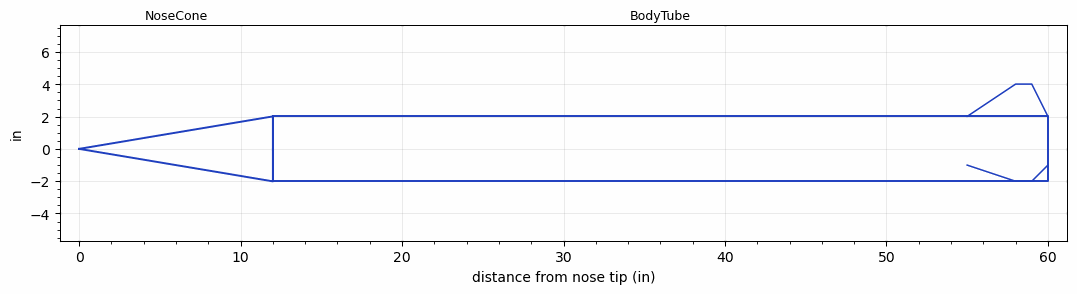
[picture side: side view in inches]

<RASAeroDocument>
 <FileVersion>2</FileVersion>
 <RocketDesign>
  <NoseCone>
   <Length>12</Length>
   <Diameter>4.024</Diameter>
   <Shape>Conical</Shape>
   <Location>0</Location>
  </NoseCone>
  <BodyTube>
   <Length>48</Length>
   <Diameter>4.024</Diameter>
   <LaunchLugDiameter>0.5</LaunchLugDiameter>
   <LaunchLugLength>0.5</LaunchLugLength>
   <Location>12</Location>
   <Fin>
    <Count>3</Count>
    <Chord>5</Chord>
    <Span>2</Span>
    <SweepDistance>3</SweepDistance>
    <TipChord>1</TipChord>
    <Thickness>0.125</Thickness>
    <LERadius>0.125</LERadius>
    <Location>5</Location>
    <AirfoilSection>Hexagonal</AirfoilSection>
    <FX1>0.125</FX1>
    <FX3>0.125</FX3>
   </Fin>
  </BodyTube>
  <Surface>Smooth (Zero Roughness)</Surface>
  <ModifiedBarrowman>False</ModifiedBarrowman>
  <Turbulence>False</Turbulence>
  <UseBooster1>False</UseBooster1>
  <UseBooster2>False</UseBooster2>
 </RocketDesign>
 <LaunchSite>
  <Altitude>3000</Altitude>
  <Pressure>30.3</Pressure>
  <RodAngle>1</RodAngle>
  <RodLength>25</RodLength>
  <Temperature>90</Temperature>
  <WindSpeed>12</WindSpeed>
 </LaunchSite>
 <Recovery>
  <Altitude1>1000</Altitude1>
  <Altitude2>1000</Altitude2>
  <DeviceType1>None</DeviceType1>
  <DeviceType2>None</DeviceType2>
  <Event1>False</Event1>
  <Event2>False</Event2>
  <Size1>1</Size1>
  <Size2>1</Size2>
  <EventType1>None</EventType1>
  <EventType2>None</EventType2>
  <CD1>1.33</CD1>
  <CD2>1.33</CD2>
 </Recovery>
 <SimulationList>
  <Simulation>
   <SustainerEngine>L1050-BS-P  (CTI)</SustainerEngine>
   <SustainerLaunchWt>40</SustainerLaunchWt>
   <SustainerNozzleDiameter>3.5</SustainerNozzleDiameter>
   <SustainerCG>30</SustainerCG>
   <SustainerIgnitionDelay>0</SustainerIgnitionDelay>
   <Booster1SeparationDelay>0</Booster1SeparationDelay>
   <Booster1IgnitionDelay>0</Booster1IgnitionDelay>
   <IncludeBooster1>False</IncludeBooster1>
   <Booster2Delay>0</Booster2Delay>
   <IncludeBooster2>False</IncludeBooster2>
   <TimetoApogee>21.95041</TimetoApogee>
   <MaxAltitude>6814.723</MaxAltitude>
   <MaxVelocity>632.792</MaxVelocity>
  </Simulation>
 </SimulationList>
</RASAeroDocument>
